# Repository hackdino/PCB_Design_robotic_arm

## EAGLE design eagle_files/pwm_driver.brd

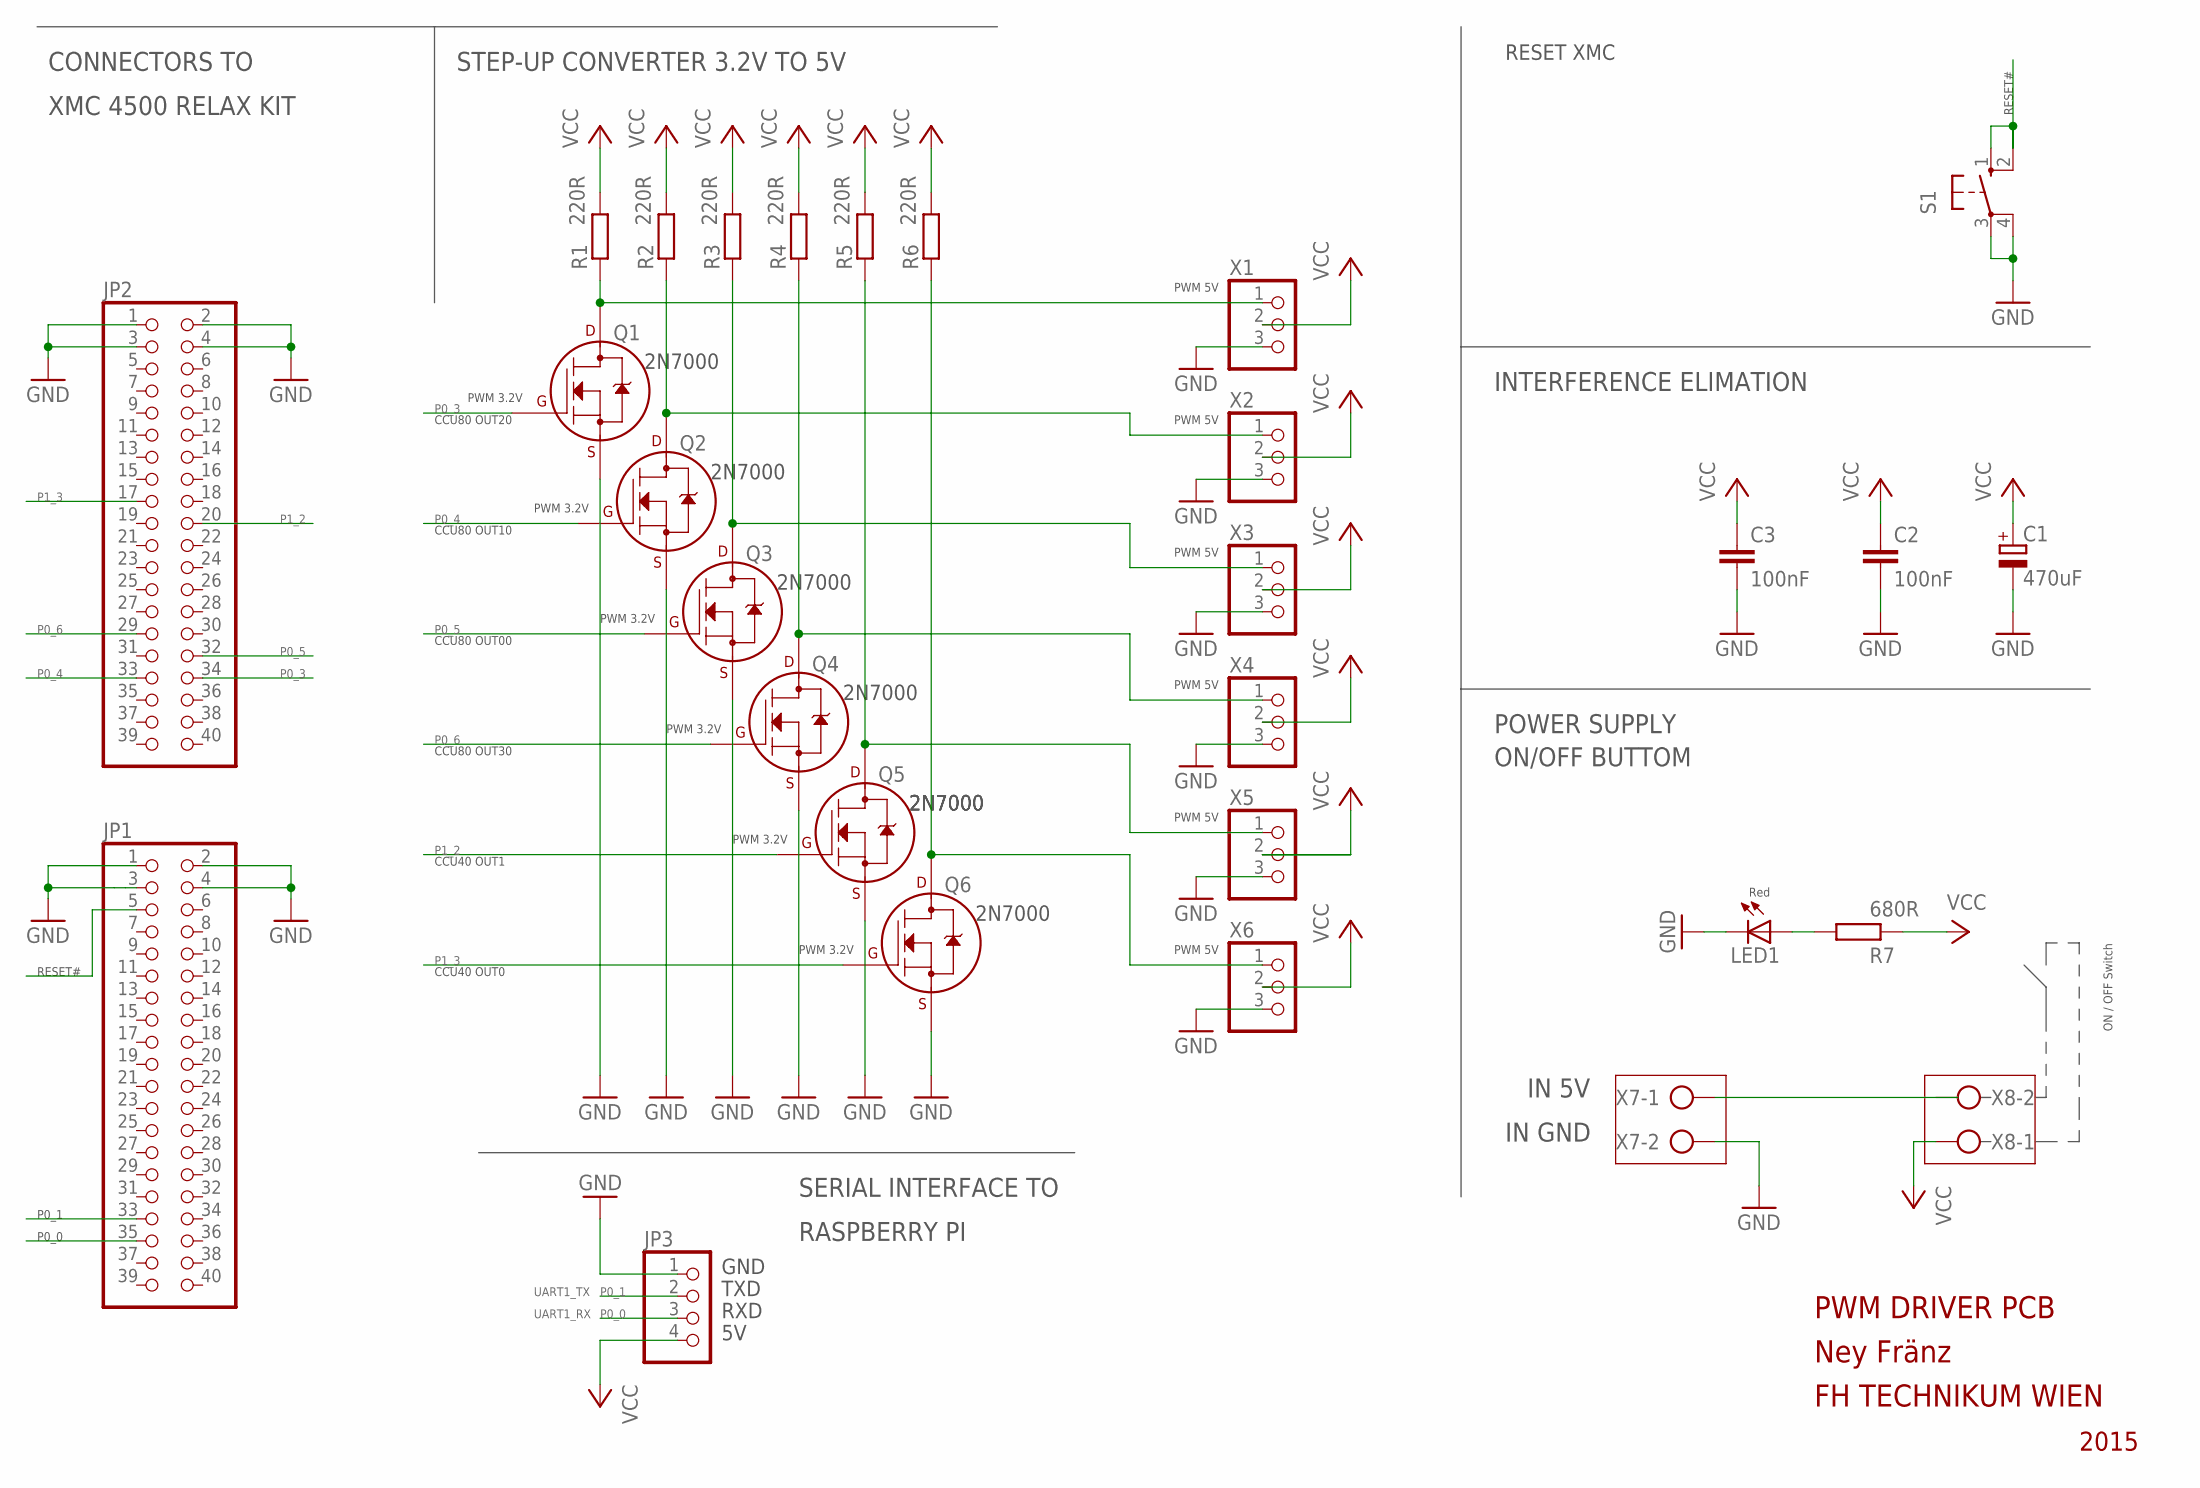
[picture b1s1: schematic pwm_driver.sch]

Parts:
C1: 470uF; E3,5-10
C2, C3: 100nF; C025-024X044
JP1, JP2: PINHD-2X20; 2X20
JP3: PINHD-1X4; 1X04
LED1: LED3MM
Q1, Q2, Q3, Q4, Q5, Q6: 2N7000_TO92; TO-92
R1, R2, R3, R4, R5, R6: 220R; 0207/10
R7: 680R; 0207/10
S1: 10-XX; B3F-10XX
X1, X2, X3, X4, X5, X6: PINHD-1X3; 1X03
X7, X8: AK500/2

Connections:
GND: C1.-, C2.2, C3.2, JP1.1, JP1.2, JP1.3, JP1.4, JP2.1, JP2.2, JP2.3, JP2.4, JP3.1, LED1.K (C), Q1.1 (S), Q2.1 (S), Q3.1 (S), Q4.1 (S), Q5.1 (S), Q6.1 (S), S1.3, S1.4 (P1), X1.3, X2.3, X3.3, X4.3, X5.3, X6.3, X7.2
unnamed: LED1.A, R7.1
unnamed: X7.1, X8.2
unnamed: Q1.3 (D), R1.1, X1.1
unnamed: Q2.3 (D), R2.1, X2.1
unnamed: Q3.3 (D), R3.1, X3.1
unnamed: Q4.3 (D), R4.1, X4.1
unnamed: Q5.3 (D), R5.1, X5.1
unnamed: Q6.3 (D), R6.1, X6.1
P0_0: JP1.35, JP3.3
P0_1: JP1.33, JP3.2
P0_3: JP2.34, Q1.2 (G)
P0_4: JP2.33, Q2.2 (G)
P0_5: JP2.32, Q3.2 (G)
P0_6: JP2.29, Q4.2 (G)
P1_2: JP2.20, Q5.2 (G)
P1_3: JP2.17, Q6.2 (G)
RESET: JP1.5, S1.1 (S), S1.2 (S1)
VCC: C1.+, C2.1, C3.1, JP3.4, R1.2, R2.2, R3.2, R4.2, R5.2, R6.2, R7.2, X1.2, X2.2, X3.2, X4.2, X5.2, X6.2, X8.1

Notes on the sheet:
2N7000
GND
PWM DRIVER PCB
Ney Fränz
FH TECHNIKUM WIEN
2015
IN 5V
IN GND
PWM 5V
PWM 3.2V
INTERFERENCE ELIMATION
POWER SUPPLY
ON/OFF BUTTOM
STEP-UP CONVERTER 3.2V TO 5V
CONNECTORS TO
XMC 4500 RELAX KIT
RASPBERRY PI
SERIAL INTERFACE TO
ON / OFF Switch
Red
P0_5
P0_3
P0_4
P0_6
P1_2
P1_3
TXD
RXD
CCU80 OUT20
CCU80 OUT10
CCU80 OUT00
CCU80 OUT30
CCU40 OUT1
CCU40 OUT0
P0_1
P0_0
UART1_TX
UART1_RX
RESET XMC
RESET#

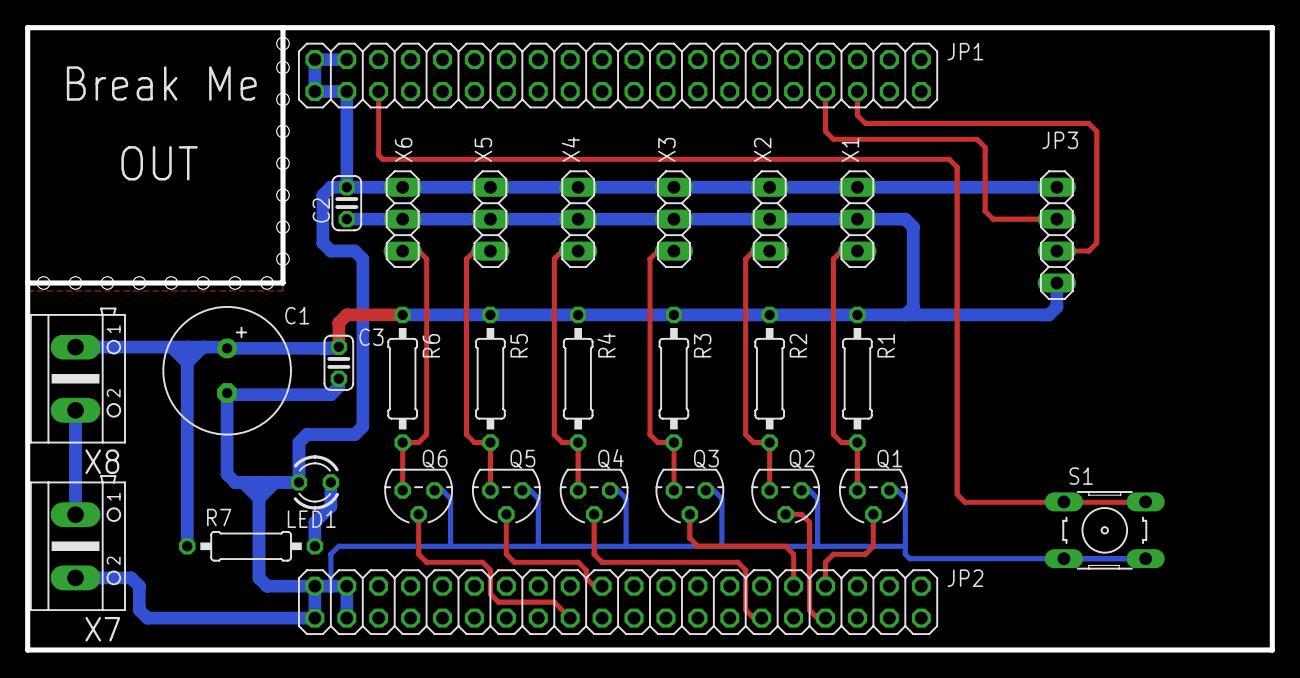
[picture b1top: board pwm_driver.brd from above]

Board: 2 copper layers, 99.1 x 49.5 mm, 29 parts (0 on the bottom side), 19 nets.
